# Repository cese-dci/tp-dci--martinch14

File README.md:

Repositorio de la materia Diseño de Circuitos Integrados de la Carrera de Especialización en Sistemas Embebidos UBA

El siguiente diseño incluye el circuito integrado TMC5130 de la empresa TRINAMIC para el manejo de motores paso a paso
conectado con el módulo del microcontrolador ESP32

Martin Abel Gambarotta
8vo Cohorte

View 3D

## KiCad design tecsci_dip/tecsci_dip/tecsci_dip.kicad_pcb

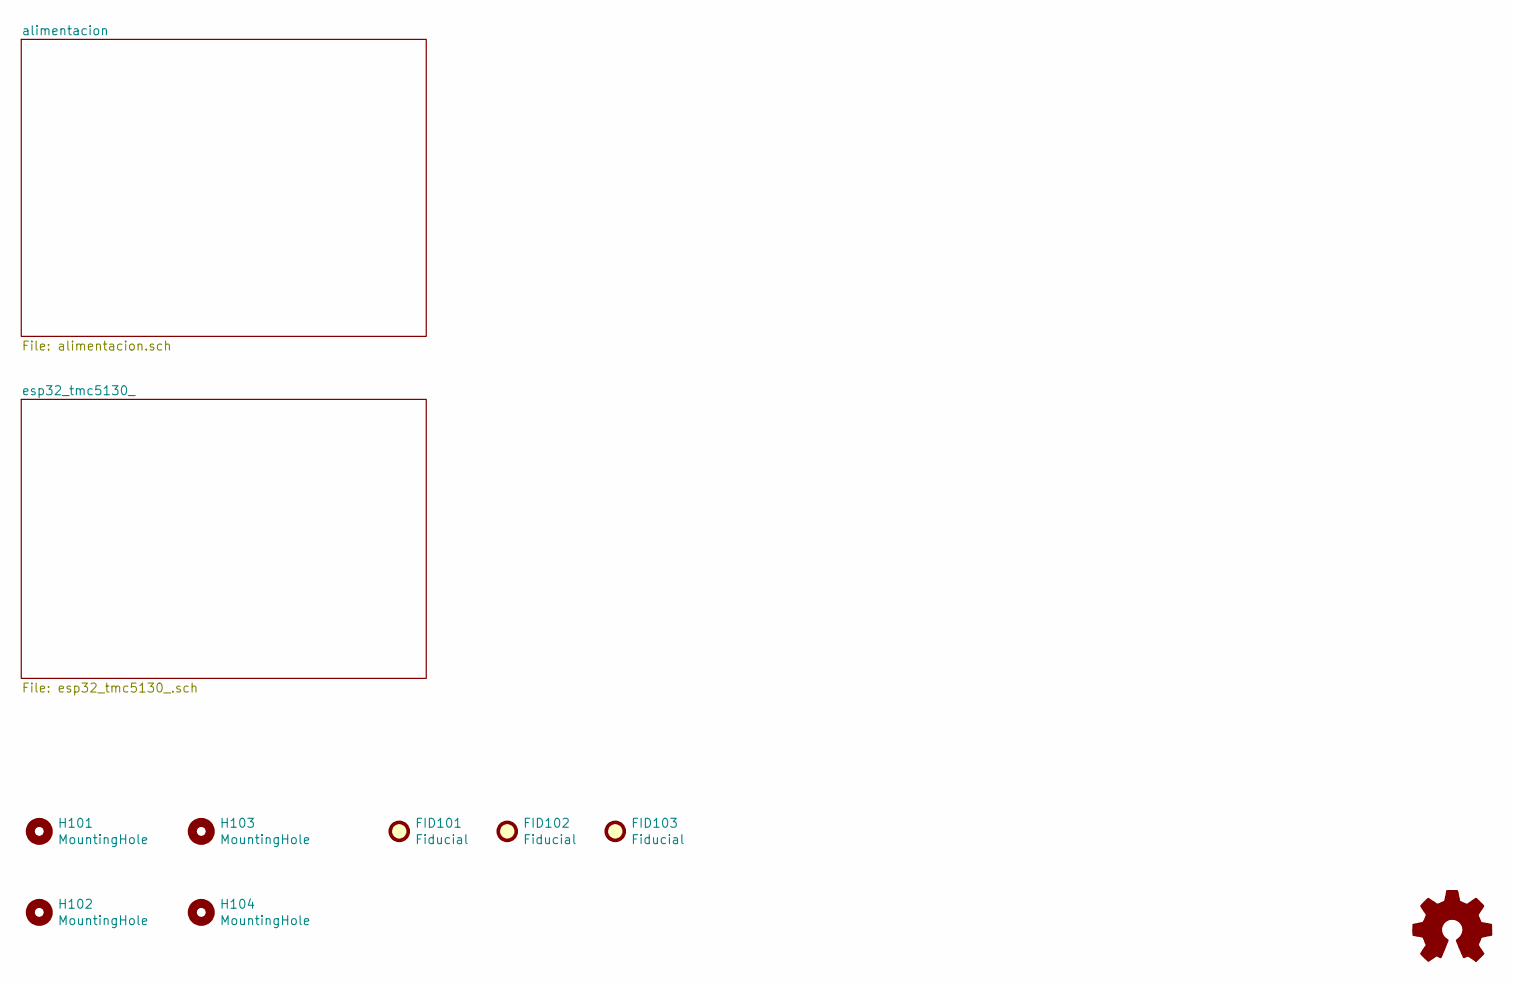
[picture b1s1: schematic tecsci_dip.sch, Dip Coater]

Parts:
FID101, FID102, FID103: Fiducial; Fiducial_1mm_Mask2mm
H101, H102, H103, H104: MountingHole; MountingHole_3.2mm_M3_Pad_Via
OSHWA101: Logo_Open_Hardware_Small; OSHW-Symbol_8.9x8mm_SilkScreen

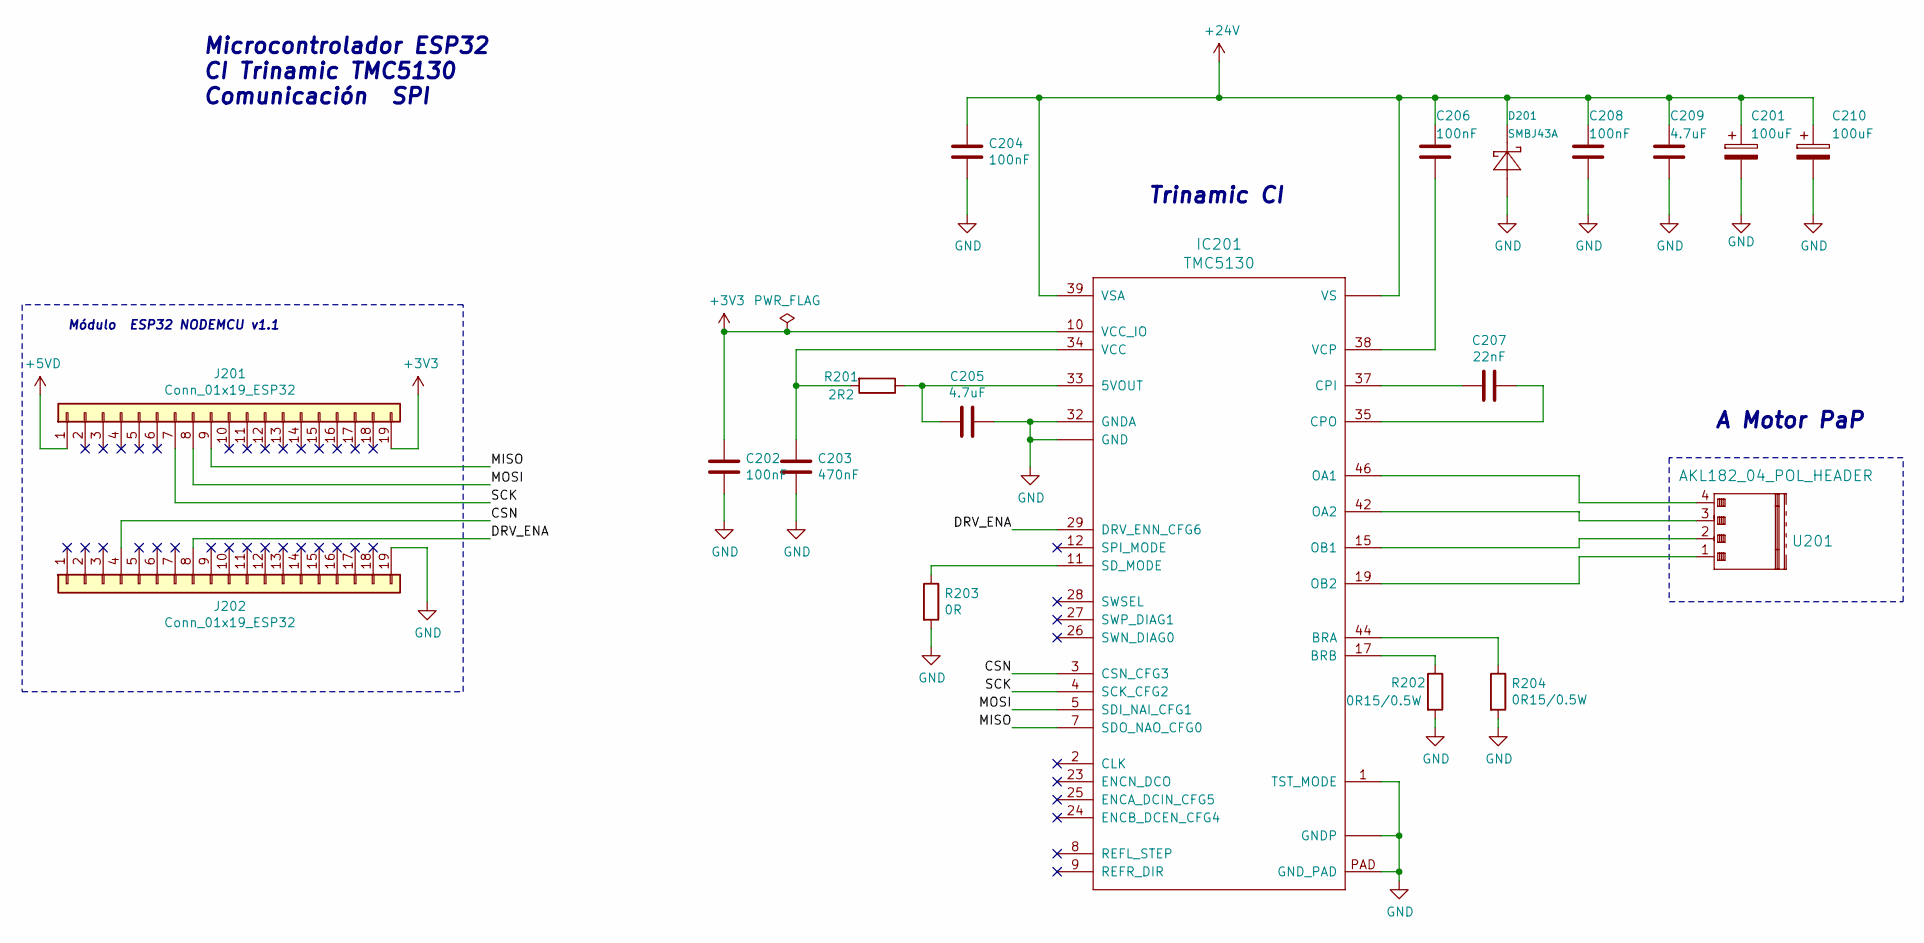
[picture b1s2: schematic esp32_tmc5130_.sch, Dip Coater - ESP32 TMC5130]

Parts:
C201, C210: 100uF; CP_Radial_D10.0mm_P7.50mm
C202, C204, C206, C208: 100nF; C_0805_2012Metric
C203: 470nF; C_0805_2012Metric
C205: 4.7uF; C_0805_2012Metric; digikey# 399-15711-2-ND
C207: 22nF; C_0805_2012Metric
C209: 4.7uF; C_1210_3225Metric
D201: SMBJ43A; SMB; digikey# SMBJ43AFSTR-ND
IC201: TMC5130; QFP50P900X900X113-49N_NOFID; digikey# 1460-1124-ND
J201, J202: Conn_01x19_ESP32; PinSocket_1x19_P2.54mm_Vertical
R201: 2R2; R_0805_2012Metric
R202, R204: 0R15/0.5W; R_1206_3216Metric
R203: 0R; R_0805_2012Metric
U201: AKL182_04_POL_HEADER; AKL169_04_POL

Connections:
+3V3: C202.1, IC201.10 (VCC_IO), J201.19
+5VD: J201.1; also elsewhere on the board
+24V: C201.1, C204.1, C206.1, C208.1, C209.1, C210.1, D201.C, IC201.21 (VS), IC201.39 (VSA), IC201.40 (VS); also elsewhere on the board
/esp32_tmc5130_/CSN: IC201.3 (CSN_CFG3), J202.4
/esp32_tmc5130_/DRV_ENA: IC201.29 (DRV_ENN_CFG6), J202.8
/esp32_tmc5130_/MISO: IC201.7 (SDO_NAO_CFG0), J201.9
/esp32_tmc5130_/MOSI: IC201.5 (SDI_NAI_CFG1), J201.8
/esp32_tmc5130_/SCK: IC201.4 (SCK_CFG2), J201.7
GND: C201.2, C202.2, C203.2, C204.2, C205.1, C208.2, C209.2, C210.2, D201.A, IC201.1 (TST_MODE), IC201.6 (GND), IC201.13 (GNDP), IC201.31 (GND), IC201.32 (GNDA), IC201.36 (GND), IC201.48 (GNDP), IC201.PAD (GND_PAD), J202.19, R202.2, R203.2, R204.2; also elsewhere on the board
unnamed: C203.1, IC201.34 (VCC), R201.2
unnamed: C205.2, IC201.33 (5VOUT), R201.1
unnamed: C206.2, IC201.38 (VCP)
unnamed: C207.1, IC201.35 (CPO)
unnamed: C207.2, IC201.37 (CPI)
unnamed: IC201.11 (SD_MODE), R203.1
unnamed: IC201.15 (OB1), U201.2
unnamed: IC201.17 (BRB), R202.1
unnamed: IC201.19 (OB2), U201.1
unnamed: IC201.42 (OA2), U201.3
unnamed: IC201.44 (BRA), R204.1
unnamed: IC201.46 (OA1), U201.4

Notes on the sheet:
Módulo ESP32 NODEMCU v1.1
Trinamic CI
A Motor PaP
Microcontrolador ESP32 CI Trinamic TMC5130 Comunicación SPI

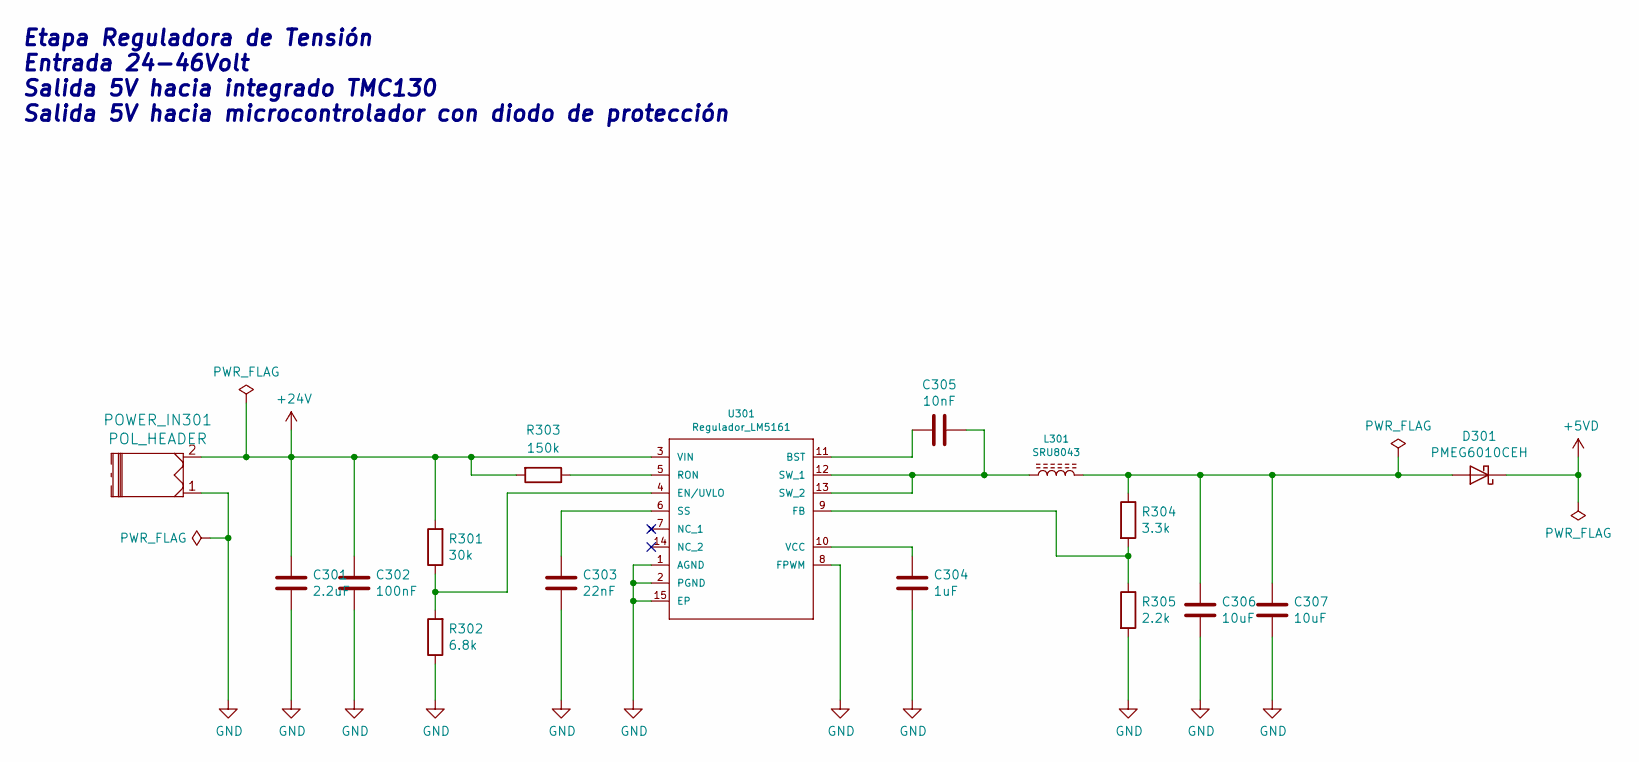
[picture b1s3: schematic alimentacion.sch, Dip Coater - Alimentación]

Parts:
C301: 2.2uF; C_1206_3216Metric
C302: 100nF; C_1206_3216Metric
C303: 22nF; C_0805_2012Metric
C304: 1uF; C_0805_2012Metric
C305: 10nF; C_0805_2012Metric
C306, C307: 10uF; C_0805_2012Metric
D301: PMEG6010CEH; D_SOD-123; digikey# 1727-3848-2-ND
L301: SRU8043; L_Bourns-SRU8043; digikey# SRU8043-100YTR-ND
POWER_IN301: POL_HEADER; AKL349_02_POL
R301: 30k; C_0805_2012Metric
R302: 6.8k; R_0805_2012Metric
R303: 150k; R_0805_2012Metric
R304: 3.3k; R_0805_2012Metric
R305: 2.2k; R_0805_2012Metric
U301: Regulador_LM5161; TSSOP-14-1EP_4.4x5mm_P0.65mm; digikey# 296-47791-2-ND

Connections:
+5VD: D301.1 (K); also elsewhere on the board
+24V: C301.1, C302.1, POWER_IN301.2, R301.2, R303.2, U301.3 (VIN); also elsewhere on the board
GND: C301.2, C302.2, C303.2, C304.2, C306.2, C307.2, POWER_IN301.1, R302.1, R305.2, U301.1 (AGND), U301.2 (PGND), U301.8 (FPWM), U301.15 (EP); also elsewhere on the board
unnamed: C303.1, U301.6 (SS)
unnamed: C304.1, U301.10 (VCC)
unnamed: C305.1, L301.1, U301.12 (SW_1), U301.13 (SW_2)
unnamed: C305.2, U301.11 (BST)
unnamed: C306.1, C307.1, D301.2 (A), L301.2, R304.1
unnamed: R301.1, R302.2, U301.4 (EN/UVLO)
unnamed: R303.1, U301.5 (RON)
unnamed: R304.2, R305.1, U301.9 (FB)

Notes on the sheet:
Etapa Reguladora de Tensión Entrada 24-46Volt Salida 5V hacia integrado TMC130 Salida 5V hacia microcontrolador con diodo de protección

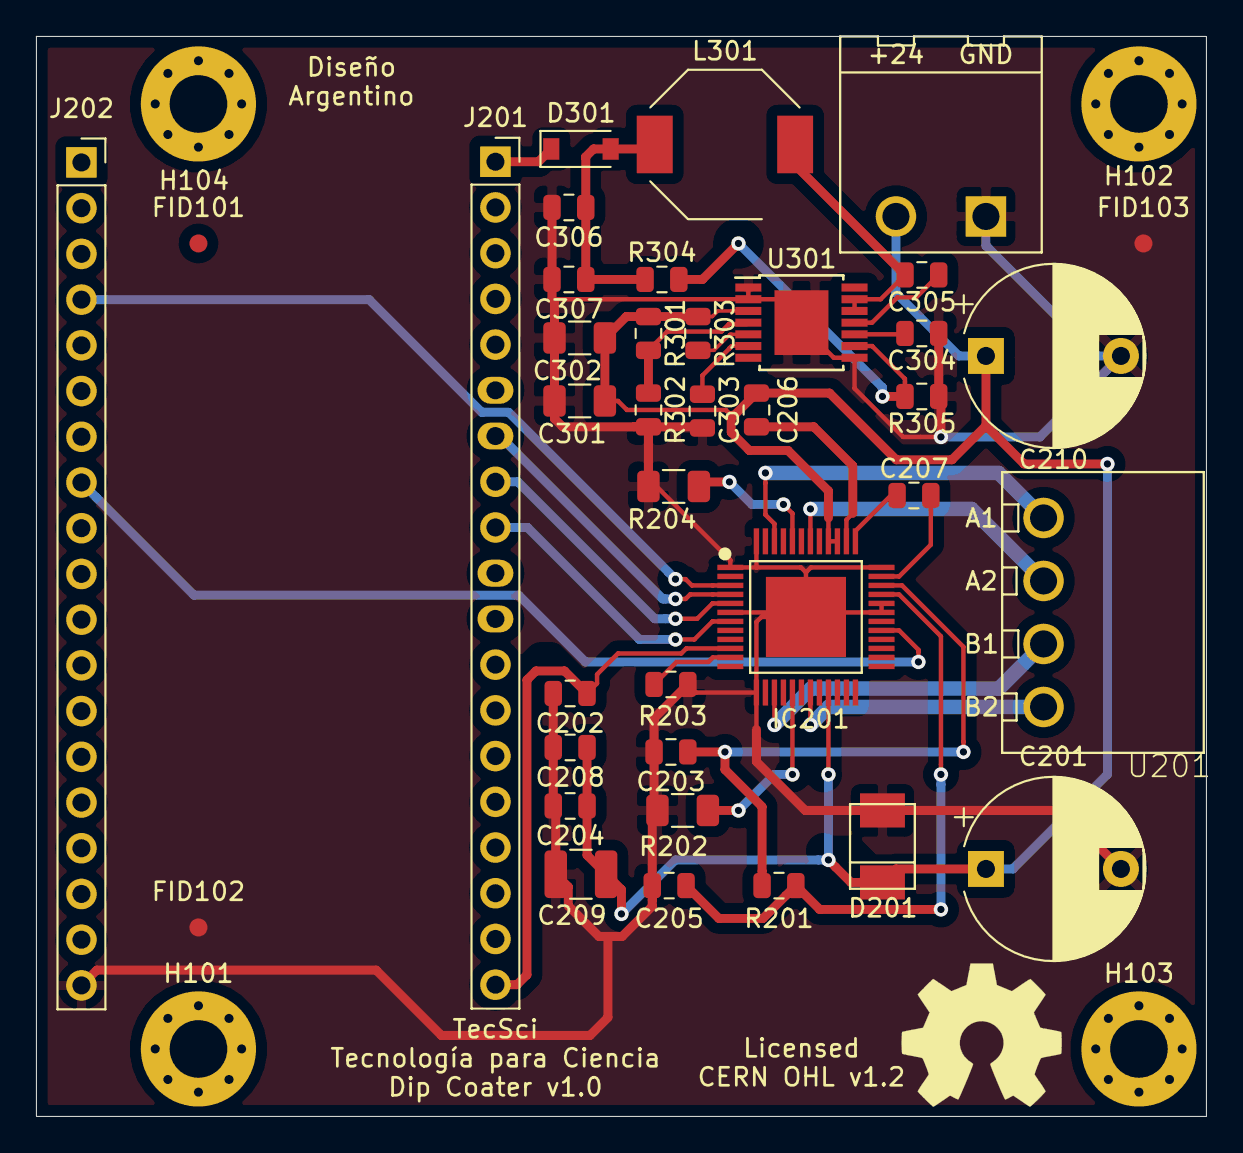
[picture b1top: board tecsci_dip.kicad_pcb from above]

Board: 2 copper layers, 65.0 x 60.0 mm, 43 parts (0 on the bottom side), 29 nets.

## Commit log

2019-09-13 Add ESP32 + Trinamic TMC5130
2019-09-13 add photos
2019-09-26 add folder info
2019-10-09 add Esquematico
2019-10-11 add value and footprint
2019-10-11 agrego valor faltantes en esquematico
2019-10-28 update board
2019-10-28 add area de cobre
2019-10-28 add fiduciales
2019-10-28 add license CERN OHL v.1.2
2019-10-28 add license
2019-10-30 add correcciones compañero
2019-10-31 Se corrigen todos los errores marcados por el profesor, excepto pasar a footprint conectores de ESP32, ya que la v2 contendra al CI
2019-11-01 arreglo en alimentacion.sch , habria con error en archivo
2019-11-01 add renders
2019-11-01 add line README.md

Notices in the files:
tecsci_dip/tecsci_dip/alimentacion.sch:
Tecsci  Tecnología para Ciencia Licensed under CERN OHL v.1.2
